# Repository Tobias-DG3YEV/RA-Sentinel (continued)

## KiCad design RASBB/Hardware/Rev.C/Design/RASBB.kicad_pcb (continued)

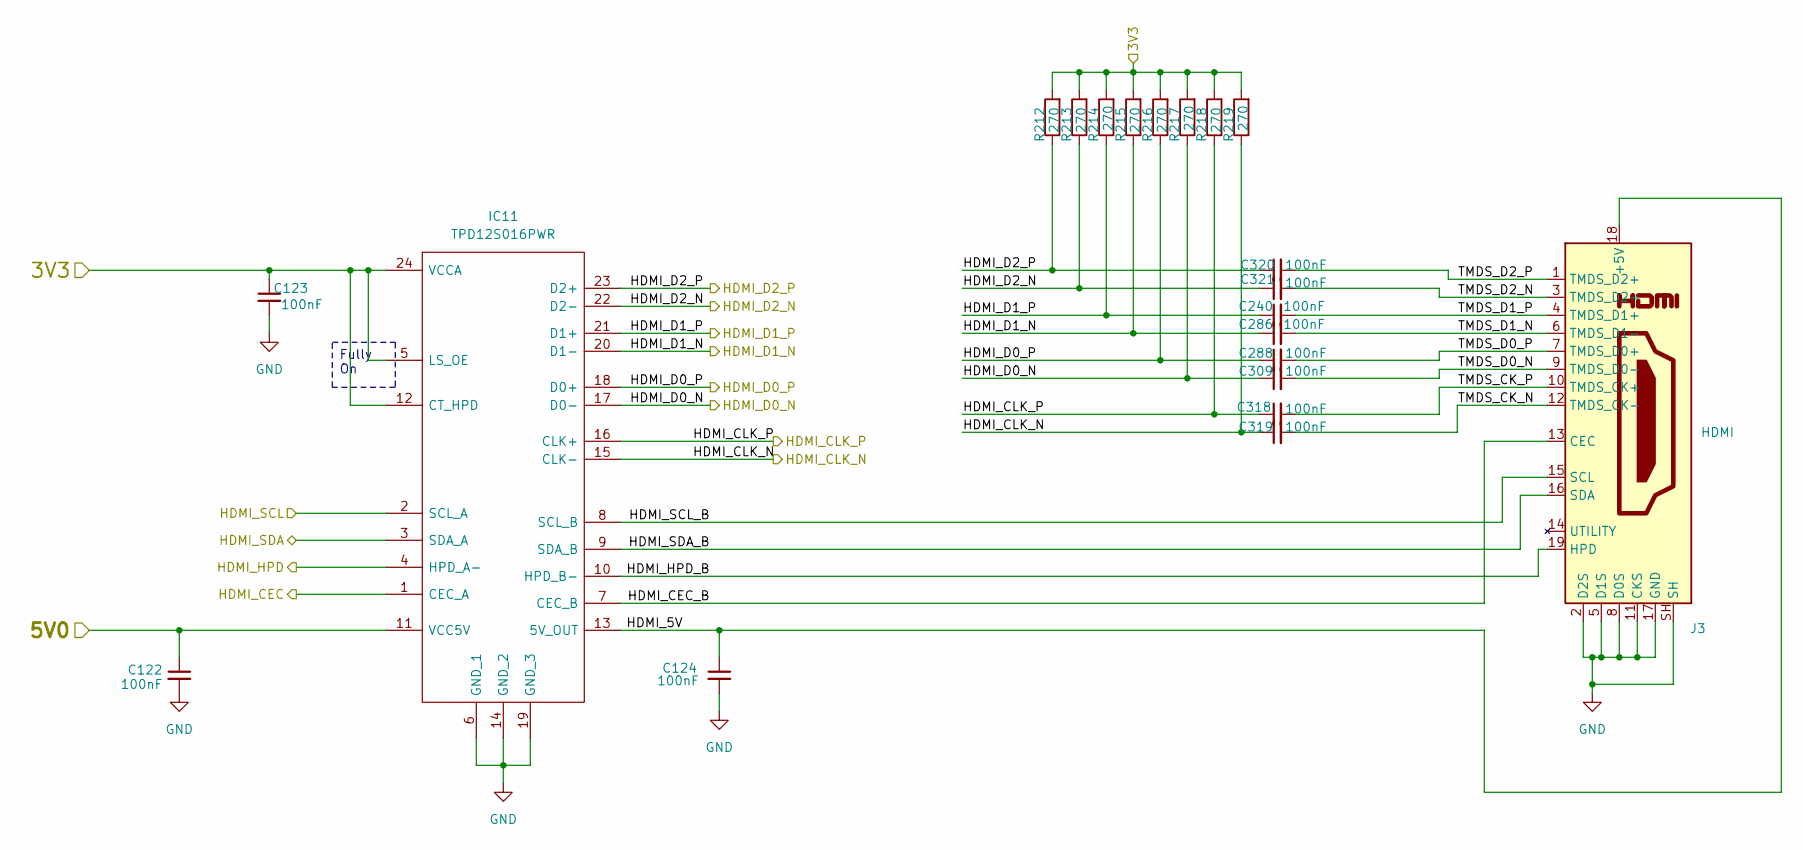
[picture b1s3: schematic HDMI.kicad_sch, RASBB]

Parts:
C122, C123, C124, C240, C286, C288, C309, C318, C319, C320, C321: 100nF; C_0402_1005Metric; Mfr. Part # 0402B104K500CT; LCSC Part # C152814
IC11: TPD12S016PWR; SOP65P640X120-24N; Mfr. Part # TPD12S016PWR; LCSC Part # C201665
J3: HDMI; HDMI-001A; Mfr. Part # HDMI-001A; LCSC Part # C41347845
R212, R213, R214, R215, R216, R217, R218, R219: 270; R_0402_1005Metric; Mfr. Part # SR04X271JTL; LCSC Part # C880838

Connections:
/Audio_IN-OUT/3V3: C123.1, IC11.5 (LS_OE), IC11.12 (CT_HPD), IC11.24 (VCCA), R212.2, R213.2, R214.2, R215.2, R216.2, R217.2, R218.2, R219.2; also elsewhere on the board
/Audio_IN-OUT/5V0: C122.1, IC11.11 (VCC5V); also elsewhere on the board
/FPGA-01/F1_B15_C15: IC11.4 (HPD_A-); also elsewhere on the board
/FPGA-01/F1_B15_D15: IC11.3 (SDA_A); also elsewhere on the board
/FPGA-01/F1_B15_E15: IC11.2 (SCL_A); also elsewhere on the board
/FPGA-01/F1_B15_E16: IC11.1 (CEC_A); also elsewhere on the board
/HDMI/HDMI_5V: C124.1, IC11.13 (5V_OUT), J3.18 (+5V)
/HDMI/HDMI_CEC_B: IC11.7 (CEC_B), J3.13 (CEC)
/HDMI/HDMI_CLK_N: C319.1, IC11.15 (CLK-), R219.1; also elsewhere on the board
/HDMI/HDMI_CLK_P: C318.1, IC11.16 (CLK+), R218.1; also elsewhere on the board
/HDMI/HDMI_D0_N: C309.1, IC11.17 (D0-), R217.1; also elsewhere on the board
/HDMI/HDMI_D0_P: C288.1, IC11.18 (D0+), R216.1; also elsewhere on the board
/HDMI/HDMI_D1_N: C286.1, IC11.20 (D1-), R215.1; also elsewhere on the board
/HDMI/HDMI_D1_P: C240.1, IC11.21 (D1+), R214.1; also elsewhere on the board
/HDMI/HDMI_D2_N: C321.1, IC11.22 (D2-), R213.1; also elsewhere on the board
/HDMI/HDMI_D2_P: C320.1, IC11.23 (D2+), R212.1; also elsewhere on the board
/HDMI/HDMI_HPD_B: IC11.10 (HPD_B-), J3.19 (HPD)
/HDMI/HDMI_SCL_B: IC11.8 (SCL_B), J3.15 (SCL)
/HDMI/HDMI_SDA_B: IC11.9 (SDA_B), J3.16 (SDA)
/HDMI/TMDS_CK_N: C319.2, J3.12 (TMDS_CK-)
/HDMI/TMDS_CK_P: C318.2, J3.10 (TMDS_CK+)
/HDMI/TMDS_D0_N: C309.2, J3.9 (TMDS_D0-)
/HDMI/TMDS_D0_P: C288.2, J3.7 (TMDS_D0+)
/HDMI/TMDS_D1_N: C286.2, J3.6 (TMDS_D1-)
/HDMI/TMDS_D1_P: C240.2, J3.4 (TMDS_D1+)
/HDMI/TMDS_D2_N: C321.2, J3.3 (TMDS_D2-)
/HDMI/TMDS_D2_P: C320.2, J3.1 (TMDS_D2+)
GND: C122.2, C123.2, C124.2, IC11.6 (GND_1), IC11.14 (GND_2), IC11.19 (GND_3), J3.2 (D2S), J3.5 (D1S), J3.8 (D0S), J3.11 (CKS), J3.17 (GND), J3.SH; also elsewhere on the board

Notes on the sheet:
Fully On

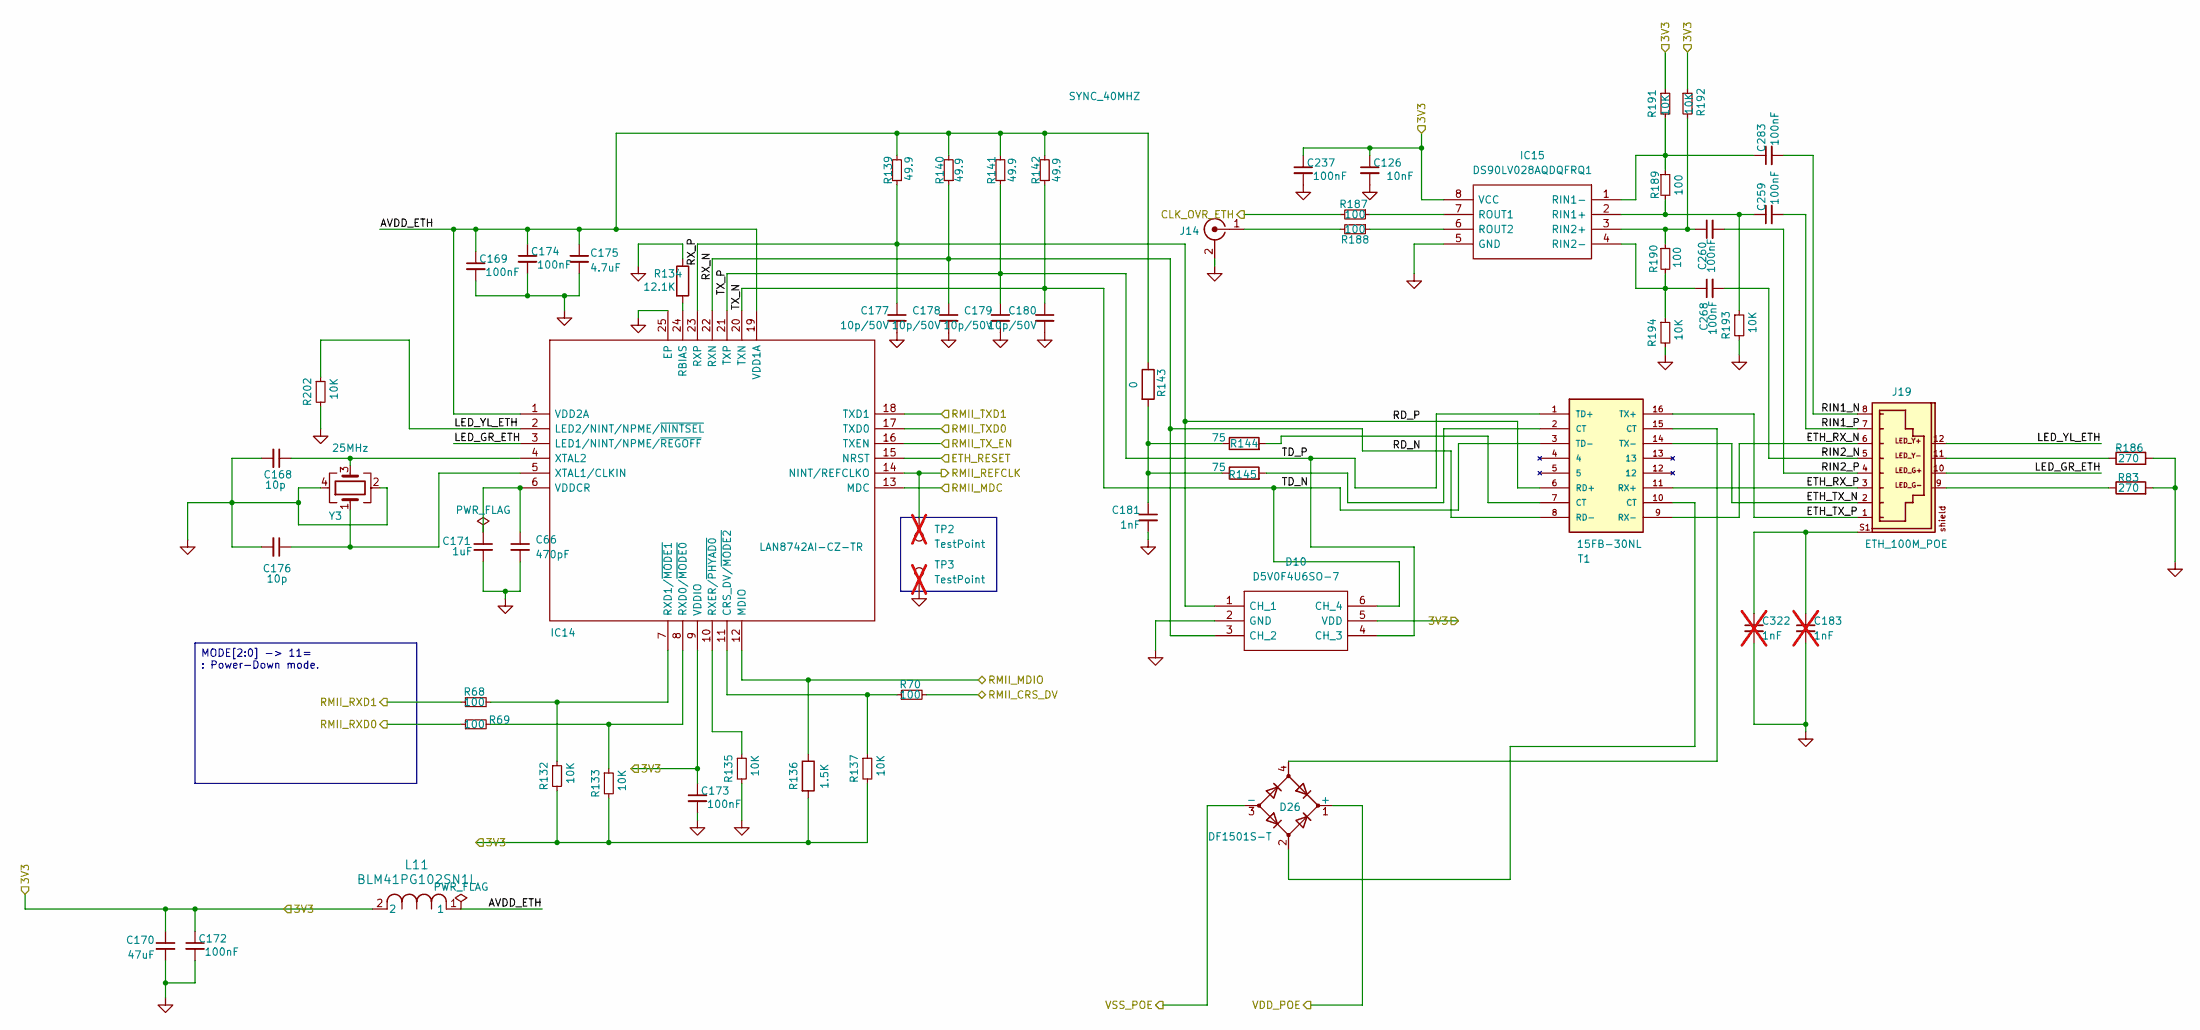
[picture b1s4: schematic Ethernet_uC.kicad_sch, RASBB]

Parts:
C66: 470pF; C_0402_1005Metric; Mfr. Part # CC0402JRNPO7BN471; LCSC Part # C526993
C126: 10nF; C_0402_1005Metric; Mfr. Part # 0402B103K500CT; LCSC Part # C301927
C168, C176: 10p; C_0402_1005Metric; Mfr. Part # 0402N100J500CT; LCSC Part # C301961
C169, C172, C173, C174, C237, C259, C260, C268, C283: 100nF; C_0402_1005Metric; Mfr. Part # 0402B104K500CT; LCSC Part # C152814
C170: 47uF; C_0805_2012Metric; Mfr. Part # GRM21BR61A476ME15L; LCSC Part # C124129
C171: 1uF; C_0402_1005Metric; Mfr. Part # 0402X105M160CT; LCSC Part # C3889771
C175: 4.7uF; C_0603_1608Metric; Mfr. Part # GMK107BBJ475KA-T; LCSC Part # C7281848
C177, C178, C179, C180: 10p/50V; C_0603_1608Metric; Mfr. Part # 0603N100J500CT; LCSC Part # C152928
C181: 1nF; C_1206_3216Metric; Mfr. Part # 1206B102K202CT; LCSC Part # C303946
C183, C322: 1nF; C_1206_3216Metric; not fitted
D10: D5V0F4U6SO-7; SOT95P285X140-6N; Mfr. Part # D5V0F4U6SO-7; LCSC Part # C445539
D26: DF1501S-T; DF1501ST; Mfr. Part # DF1501S-T; LCSC Part # C155338
IC14: LAN8742AI-CZ-TR; QFN50P400X400X100-25N-D; Mfr. Part # LAN8742AI-CZ-TR; LCSC Part # C621425
IC15: DS90LV028AQDQFRQ1; SON50P200X200X80-8N; Mouser Part Number 595-S90LV028AQDQFRQ1
J14: SYNC_40MHZ; J_Wurth_WR-UMRF_636101112001; Mfr. Part # 636101112001
J19: ETH_100M_POE; HC-WK88-H16-DB; Mfr. Part # HC-WK88-H16-DB; LCSC Part # C7501824
L11: BLM41PG102SN1L; IND_BLM41_1806_MUR-M; Mfr. Part # BLM41PG102SN1L; LCSC Part # C88999
R68, R69, R70, R187, R188, R189, R190: 100; R_0402_1005Metric; Mfr. Part # WR04X1000FTL; LCSC Part # C163808
R83, R186: 270; R_0402_1005Metric; Mfr. Part # SR04X271JTL; LCSC Part # C880838
R132, R133, R135, R137, R191, R192, R193, R194, R202: 10K; R_0402_1005Metric; Mfr. Part # WR04X1002FTL; LCSC Part # C163810
R134: 12.1K; R_0402_1005Metric; Mfr. Part # WR04X1212FTL; LCSC Part # C168199
R136: 1.5K; R_0402_1005Metric; Mfr. Part # WR04X152JTL; LCSC Part # C384376
R139, R140, R141, R142: 49.9; R_0402_1005Metric; Mfr. Part # RMCF0402FT49R9; LCSC Part # C4229190
R143: 0; R_0603_1608Metric; Mfr. Part # RCS06030000Z0EC; LCSC Part # C2094997
R144, R145: 75; R_0603_1608Metric; Mfr. Part # ESR03EZPF75R0; LCSC Part # C2074227
T1: 15FB-30NL; SOIC127P940X597-16N; Mfr. Part # 15FB-30NL; LCSC Part # C2987675
TP2, TP3: TestPoint; TestPoint_Pad_D1.0mm; not fitted
Y3: 25MHz; Crystal_SMD_3225-4Pin_3.2x2.5mm; Mfr. Part # XL2EL89CSI-111YLC-25M; LCSC Part # C5280577

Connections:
/Audio_IN-OUT/3V3: C126.1, C170.1, C172.1, C173.1, C237.1, D10.5 (VDD), IC14.9 (VDDIO), IC15.8 (VCC), L11.2, R132.2, R133.2, R136.2, R137.2, R191.1, R192.1; also elsewhere on the board
/CLK_OVR_ETH: R187.2; also elsewhere on the board
/Ethernet_uC/AVDD_ETH: C169.1, C174.1, C175.1, IC14.1 (VDD2A), IC14.19 (VDD1A), L11.1, R139.2, R140.2, R141.2, R142.2, R143.1
/Ethernet_uC/ETH_RESET: IC14.15 (NRST); also elsewhere on the board
/Ethernet_uC/ETH_RX_N: J19.6, T1.9 (RX-)
/Ethernet_uC/ETH_RX_P: J19.3, T1.11 (RX+)
/Ethernet_uC/ETH_TX_N: J19.2, T1.14 (TX-)
/Ethernet_uC/ETH_TX_P: J19.1, T1.16 (TX+)
/Ethernet_uC/LED_GR_ETH: IC14.3 (LED1/NINT/NPME/~REGOFF), J19.10
/Ethernet_uC/LED_YL_ETH: IC14.2 (LED2/NINT/NPME/~NINTSEL), J19.12, R202.1
/Ethernet_uC/RD_N: C178.1, D10.3 (CH_2), IC14.22 (RXN), R140.1, T1.8 (RD-)
/Ethernet_uC/RD_P: C177.1, D10.1 (CH_1), IC14.23 (RXP), R139.1, T1.6 (RD+)
/Ethernet_uC/RIN1_N: C283.2, J19.8
/Ethernet_uC/RIN1_P: C259.2, J19.7
/Ethernet_uC/RIN2_N: C268.2, J19.5
/Ethernet_uC/RIN2_P: C260.2, J19.4
/Ethernet_uC/RMII_CRS_DV: R70.2; also elsewhere on the board
/Ethernet_uC/RMII_MDC: IC14.13 (MDC); also elsewhere on the board
/Ethernet_uC/RMII_MDIO: IC14.12 (MDIO), R136.1; also elsewhere on the board
/Ethernet_uC/RMII_REFCLK: IC14.14 (NINT/REFCLKO), TP2.1 (1_1); also elsewhere on the board
/Ethernet_uC/RMII_RXD0: R69.1; also elsewhere on the board
/Ethernet_uC/RMII_RXD1: R68.1; also elsewhere on the board
/Ethernet_uC/RMII_TXD0: IC14.17 (TXD0); also elsewhere on the board
/Ethernet_uC/RMII_TXD1: IC14.18 (TXD1); also elsewhere on the board
/Ethernet_uC/RMII_TX_EN: IC14.16 (TXEN); also elsewhere on the board
/Ethernet_uC/TD_N: C180.1, D10.6 (CH_4), IC14.20 (TXN), R142.1, T1.3 (TD-)
/Ethernet_uC/TD_P: C179.1, D10.4 (CH_3), IC14.21 (TXP), R141.1, T1.1 (TD+)
/VDC_IN: D26.1 (+); also elsewhere on the board
/VSS_POE: D26.3 (-); also elsewhere on the board
GND: C66.2, C126.2, C168.2, C169.2, C170.2, C171.2, C172.2, C173.2, C174.2, C175.2, C176.2, C177.2, C178.2, C179.2, C180.2, C181.2, C183.2, C237.2, C322.2, D10.2 (GND), IC14.25 (EP), IC15.5 (GND), J14.2 (Ext), R83.2, R134.1, R135.2, R186.2, R193.2, R194.2, R202.2, TP3.1 (1_1), Y3.2, Y3.4; also elsewhere on the board
unnamed: C181.1, R143.2, R144.1, R145.1
unnamed: C183.1, C322.1, J19.S1, J19.S2
unnamed: D26.2, T1.10 (CT)
unnamed: D26.4, T1.15 (CT)
unnamed: IC14.11 (CRS_DV/~MODE2), R70.1, R137.1
unnamed: IC14.24 (RBIAS), R134.2
unnamed: IC14.8 (RXD0/~MODE0), R69.2, R133.1
unnamed: IC14.7 (RXD1/~MODE1), R68.2, R132.1
unnamed: IC14.10 (RXER/~PHYAD0), R135.1
unnamed: C66.1, C171.1, IC14.6 (VDDCR)
unnamed: C176.1, IC14.5 (XTAL1/CLKIN), Y3.1
unnamed: C168.1, IC14.4 (XTAL2), Y3.3
unnamed: C259.1, IC15.2 (RIN1+), R189.2, R193.1
unnamed: C283.1, IC15.1 (RIN1-), R189.1, R191.2
unnamed: C260.1, IC15.3 (RIN2+), R190.1, R192.2
unnamed: C268.1, IC15.4 (RIN2-), R190.2, R194.1
unnamed: IC15.7 (ROUT1), R187.1
unnamed: IC15.6 (ROUT2), R188.1
unnamed: J14.1 (In), R188.2
unnamed: J19.9, R83.1
unnamed: J19.11, R186.1
unnamed: R144.2, T1.7 (CT)
unnamed: R145.2, T1.2 (CT)

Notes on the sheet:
MODE[2:0] -> 11= : Power-Down mode.

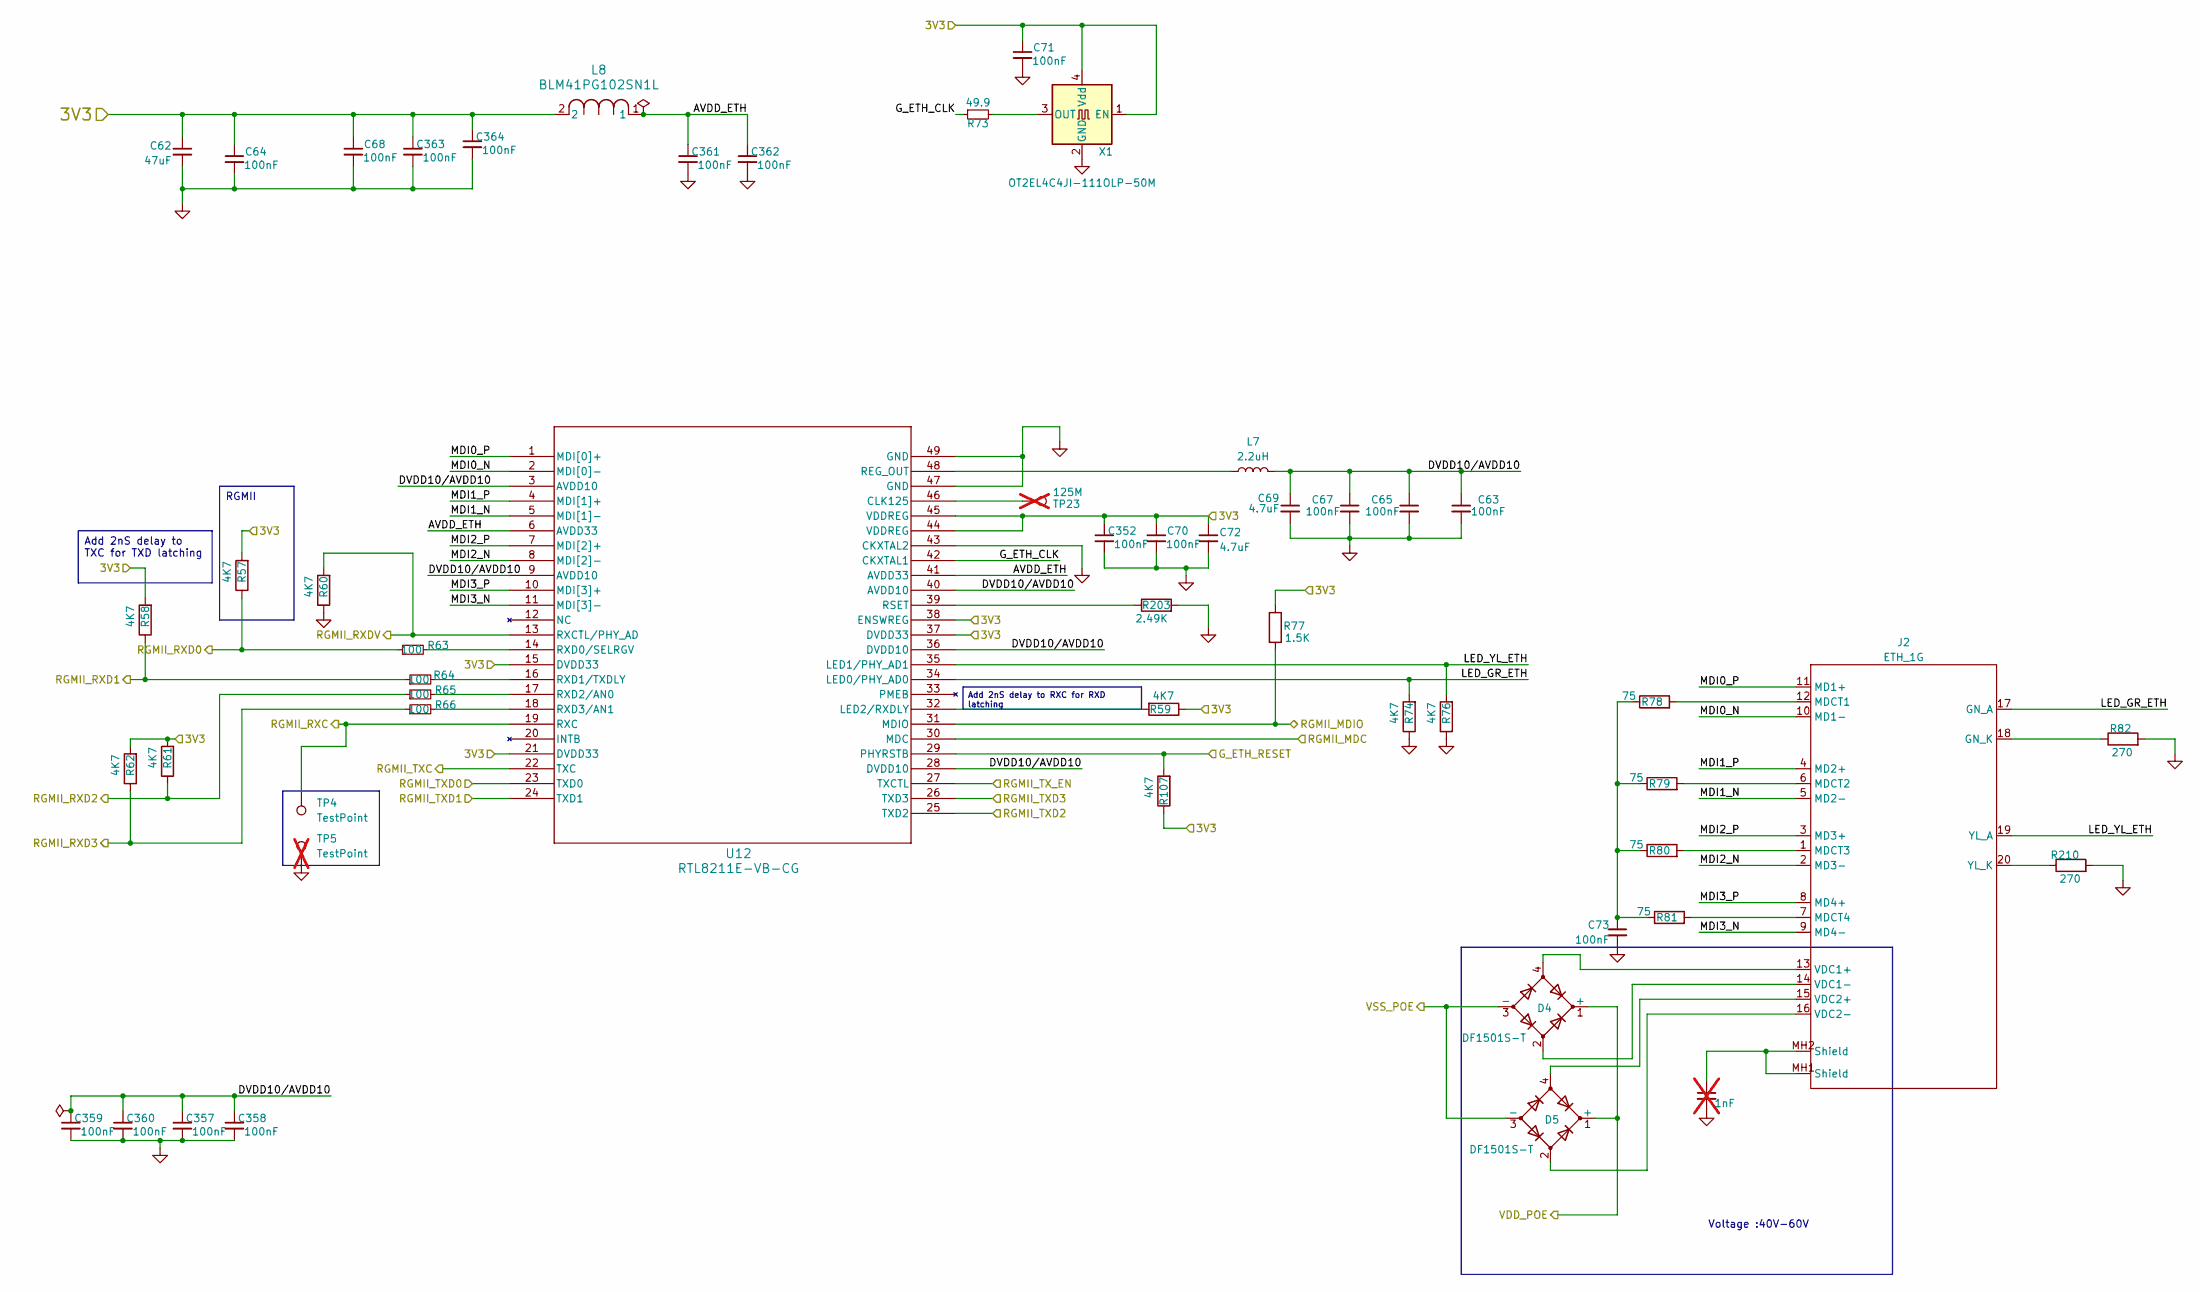
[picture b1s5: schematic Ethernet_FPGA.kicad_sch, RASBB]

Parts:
C62: 47uF; C_0805_2012Metric; Mfr. Part # GRM21BR61A476ME15L; LCSC Part # C124129
C63, C64, C65, C67, C68, C70, C71, C352, C357, C358, C359, C360, C361, C362, C363, C364: 100nF; C_0402_1005Metric; Mfr. Part # 0402B104K500CT; LCSC Part # C152814
C69, C72: 4.7uF; C_0402_1005Metric; Mfr. Part # GRM155R61A475KEAAD; LCSC Part # C77004
C73: 100nF; C_2220_5750Metric; Mfr. Part # FV55X104K202EGG; LCSC Part # C5290327
C74: 1nF; C_1206_3216Metric; not fitted
D4, D5: DF1501S-T; DF1501ST; Mfr. Part # DF1501S-T; LCSC Part # C155338
J2: ETH_1G; JK00229NL; Mfr. Part # HR911196AE; LCSC Part # C5149194
L7: 2.2uH; L_1206_3216Metric; Mfr. Part # MGFL3216F2R2MT-LF; LCSC Part # C486337
L8: BLM41PG102SN1L; IND_BLM41_1806_MUR-M; Mfr. Part # BLM41PG102SN1L; LCSC Part # C88999
R57, R58, R59, R60, R61, R62, R74, R76, R107: 4K7; R_0402_1005Metric; Mfr. Part # WR04X4701FTL; LCSC Part # C163826
R63, R64, R65, R66: 100; R_0402_1005Metric; Mfr. Part # WR04X1000FTL; LCSC Part # C163808
R73: 49.9; R_0402_1005Metric; Mfr. Part # RMCF0402FT49R9; LCSC Part # C4229190
R77: 1.5K; R_0402_1005Metric; Mfr. Part # WR04X152JTL; LCSC Part # C384376
R78, R79, R80, R81: 75; R_0603_1608Metric; Mfr. Part # ESR03EZPF75R0; LCSC Part # C2074227
R82, R210: 270; R_0402_1005Metric; Mfr. Part # SR04X271JTL; LCSC Part # C880838
R203: 2.49K; R_0402_1005Metric; Mfr. Part # RC0402FR-072K49L; LCSC Part # C145071
TP4: TestPoint; TestPoint_Pad_D1.0mm
TP5: TestPoint; TestPoint_Pad_D1.0mm; not fitted
TP23: 125M; TestPoint_Pad_D1.0mm; not fitted
U12: RTL8211E-VB-CG; QFN48_6X6X0P85_RTK; Mfr. Part # RTL8211E-VB-CG; LCSC Part # C90735
X1: OT2EL4C4JI-111OLP-50M; Oscillator_SMD_Abracon_ASE-4Pin_3.2x2.5mm; Mfr. Part # OT2EL4C4JI-111OLP-50M; LCSC Part # C5203552

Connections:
/Audio_IN-OUT/3V3: C62.1, C64.1, C68.1, C70.1, C71.1, C72.1, C352.1, C363.1, C364.1, L8.2, R57.2, R58.2, R59.1, R61.2, R62.2, R77.1, R107.1, U12.15 (DVDD33), U12.21 (DVDD33), U12.37 (DVDD33), U12.38 (ENSWREG), U12.44 (VDDREG), U12.45 (VDDREG), X1.1 (EN), X1.4 (Vdd); also elsewhere on the board
/Ethernet_FPGA/AVDD_ETH: C361.1, C362.1, L8.1, U12.6 (AVDD33), U12.41 (AVDD33)
/Ethernet_FPGA/DVDD10/AVDD10: C63.1, C65.1, C67.1, C69.1, C357.1, C358.1, C359.1, C360.1, L7.1, U12.3 (AVDD10), U12.9 (AVDD10), U12.28 (DVDD10), U12.36 (DVDD10), U12.40 (AVDD10)
/Ethernet_FPGA/G_ETH_CLK: R73.1, U12.42 (CKXTAL1)
/Ethernet_FPGA/G_ETH_RESET: R107.2, U12.29 (PHYRSTB); also elsewhere on the board
/Ethernet_FPGA/LED_GR_ETH: J2.17 (GN_A), R74.2, U12.34 (LED0/PHY_AD0)
/Ethernet_FPGA/LED_YL_ETH: J2.19 (YL_A), R76.2, U12.35 (LED1/PHY_AD1)
/Ethernet_FPGA/MDI0_N: J2.10 (MD1-), U12.2 (MDI[0]-)
/Ethernet_FPGA/MDI0_P: J2.11 (MD1+), U12.1 (MDI[0]+)
/Ethernet_FPGA/MDI1_N: J2.5 (MD2-), U12.5 (MDI[1]-)
/Ethernet_FPGA/MDI1_P: J2.4 (MD2+), U12.4 (MDI[1]+)
/Ethernet_FPGA/MDI2_N: J2.2 (MD3-), U12.8 (MDI[2]-)
/Ethernet_FPGA/MDI2_P: J2.3 (MD3+), U12.7 (MDI[2]+)
/Ethernet_FPGA/MDI3_N: J2.9 (MD4-), U12.11 (MDI[3]-)
/Ethernet_FPGA/MDI3_P: J2.8 (MD4+), U12.10 (MDI[3]+)
/Ethernet_FPGA/RGMII_MDC: U12.30 (MDC); also elsewhere on the board
/Ethernet_FPGA/RGMII_MDIO: R77.2, U12.31 (MDIO); also elsewhere on the board
/Ethernet_FPGA/RGMII_RXC: TP4.1 (1_1), U12.19 (RXC); also elsewhere on the board
/Ethernet_FPGA/RGMII_RXD0: R57.1, R63.1; also elsewhere on the board
/Ethernet_FPGA/RGMII_RXD1: R58.1, R64.1; also elsewhere on the board
/Ethernet_FPGA/RGMII_RXD2: R61.1, R65.1; also elsewhere on the board
/Ethernet_FPGA/RGMII_RXD3: R62.1, R66.1; also elsewhere on the board
/Ethernet_FPGA/RGMII_RXDV: R60.2, U12.13 (RXCTL/PHY_AD); also elsewhere on the board
/Ethernet_FPGA/RGMII_TXC: U12.22 (TXC); also elsewhere on the board
/Ethernet_FPGA/RGMII_TXD0: U12.23 (TXD0); also elsewhere on the board
/Ethernet_FPGA/RGMII_TXD1: U12.24 (TXD1); also elsewhere on the board
/Ethernet_FPGA/RGMII_TXD2: U12.25 (TXD2); also elsewhere on the board
/Ethernet_FPGA/RGMII_TXD3: U12.26 (TXD3); also elsewhere on the board
/Ethernet_FPGA/RGMII_TX_EN: U12.27 (TXCTL); also elsewhere on the board
/VDC_IN: D4.1 (+), D5.1 (+); also elsewhere on the board
/VSS_POE: D4.3 (-), D5.3 (-); also elsewhere on the board
GND: C62.2, C63.2, C64.2, C65.2, C67.2, C68.2, C69.2, C70.2, C71.2, C72.2, C73.2, C74.2, C352.2, C357.2, C358.2, C359.2, C360.2, C361.2, C362.2, C363.2, C364.2, R60.1, R74.1, R76.1, R82.2, R203.2, R210.2, TP5.1 (1_1), U12.43 (CKXTAL2), U12.47 (GND), U12.49 (GND), X1.2 (GND); also elsewhere on the board
unnamed: C73.1, R78.1, R79.1, R80.1, R81.1
unnamed: C74.1, J2.MH1 (Shield), J2.MH2 (Shield)
unnamed: J2.18 (GN_K), R82.1
unnamed: J2.12 (MDCT1), R78.2
unnamed: J2.6 (MDCT2), R79.2
unnamed: J2.1 (MDCT3), R80.2
unnamed: J2.7 (MDCT4), R81.2
unnamed: D4.4, J2.13 (VDC1+)
unnamed: D4.2, J2.14 (VDC1-)
unnamed: D5.4, J2.15 (VDC2+)
unnamed: D5.2, J2.16 (VDC2-)
unnamed: J2.20 (YL_K), R210.1
unnamed: TP23.1 (1_1), U12.46 (CLK125)
unnamed: R59.2, U12.32 (LED2/RXDLY)
unnamed: L7.2, U12.48 (REG_OUT)
unnamed: R203.1, U12.39 (RSET)
unnamed: R63.2, U12.14 (RXD0/SELRGV)
unnamed: R64.2, U12.16 (RXD1/TXDLY)
unnamed: R65.2, U12.17 (RXD2/AN0)
unnamed: R66.2, U12.18 (RXD3/AN1)
unnamed: R73.2, X1.3 (OUT)

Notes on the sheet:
Voltage :40V-60V
Add 2nS delay to TXC for TXD latching
RGMII
Add 2nS delay to RXC for RXD latching
